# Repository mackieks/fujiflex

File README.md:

<picture> <source media="(prefers-color-scheme: dark)" srcset="images/logo.png">  </picture> 

OSHW GCVideo DVI flex for Nintendo Wii. Tested and working! Solderpad Hardware License v2.1

Special thanks to [loopj](https://github.com/loopj) for testing the FPC and writing the assembly+install documentation!

## fujiflex features
- [x] Compact 28 x 30mm 2-layer flex PCB (requires KiCAD 8.0 or later)
- [x] ~$10 BOM cost
- [x] Powered from 3.3V and 1.8V (1.2V generated from 1.8V)
- [x] 34mA @ 3.3V + 63mA @ 1.8V = 225mW power consumption
- [x] 19-pin Molex 5052781933 / 5052781970 ZIF for HDMI output
- [x] Wii SDA and SCL testpoints
- [x] MODE solder jumper
- [x] Powered by [Ingo Korb's](https://github.com/ikorb) [GCVideo DVI](https://github.com/ikorb/gcvideo/)

## Ordering & Assembly
- Download the latest gerber ZIP from [the gerbers folder](https://github.com/mackieks/fujiflex/tree/main/Gerbers).
- Order design as a 2-layer flexible PCB from JLCPCB, PCBWay, GoldPhoenix, or OSHPark.
- **MANDATORY:** FPC must use at least **0.5oz/in² copper** 
- If ordering from JLCPCB, you **must** select **0.12mm thickness** to get 0.5oz!
- A steel solderpaste stencil with etching or electropolishing is **highly** recommended for assembly. JLCPCB is a good source.

I maintain [a Mouser project](https://www.mouser.com/ProjectManager/ProjectDetail.aspx?AccessID=5589d512f3) with most of the BOM. You still need to source the FPGA from elsewhere. I suggest either [LCSC](https://www.lcsc.com/product-detail/Programmable-Logic-Device-CPLDs-FPGAs_XILINX-XC3S200A-4VQG100C_C1521645.html), [AliExpress](https://www.aliexpress.us/item/3256805017536134.html), or [Taobao](https://item.taobao.com/item.htm?abbucket=5&id=749261010737&ns=1&spm=a21n57.1.0.0.2b93523ch7BSfI).

The total BOM cost for fujiflex is around 10USD. **If you're paying more than $5 per FPGA, you are being ripped off!**

Use the provided [ibom.html](https://github.com/mackieks/fujiflex/blob/main/ibom.html) to guide part placement.

**Note:** If you intend to program the SPI flash in-system, do not place R6. You will need to place it after programming is complete.

## Flashing GCVideo

Once assembled, you'll need to flash the GCVideo bitstream. The cheap 'n' easy approach is to program *in-system* using a SPI flash programmer (EZP20xx, CH341A-based, RPi Pico) soldered to the testpads on fujiflex.

- Remove R6 to avoid powering the FPGA during programming
- Wire the CS, MISO, MOSI, CLK, and GND pads to the corresponding pins on your SPI flash programmer
- Wire the rightmost pad of R6 to 3.3V on your SPI flash programmer
- Download the *shuriken-v3-wii* bitstream from [GCVideo's latest release](https://github.com/ikorb/gcvideo/releases/latest)
- Write the bitstream (eg. `gcvideo-dvi-shuriken-v3-wii-3.1-spirom-complete.bin`) to the SPI flash (see below)
- Populate R6 (0402 0Ω)

### EZP20xx programmers

If you are using an EZP20xx programmer, you can flash the bitstream using the [Windows software](https://www.chipsetpro.com/en/content/7-download-software) for these devices.

### Other programmers (using `flashrom`)

For other programmers, [flashrom](https://flashrom.org) is an open source command line tool for programming flash chips which supports [tons of devices](https://wiki.flashrom.org/Supported_programmers), including the inexpensive CH341A-based boards.

First expand the GCVideo bitstream to match the size of the SPI flash chip:

```sh
fallocate -l 512k gcvideo-dvi-shuriken-v3-wii-3.1-spirom-complete.bin
````

Then flash the bitstream, for example with a CH341A programmer:

```sh
flashrom --programmer ch341a_spi -w gcvideo-dvi-shuriken-v3-wii-3.1-spirom-complete.bin
```

### Socket adapters

You can also use a DFN8 2x3mm socket to program the SPI flash before soldering it to the board. [Type 1](https://www.aliexpress.us/item/3256802266989931.html), [Type 2](https://www.aliexpress.us/item/3256801780444965.html)

## Installation

fujiflex is soldered directly to the [digital A/V vias](https://github.com/ikorb/gcvideo/blob/main/HDL/gcvideo_dvi/README-Wii.md#digital-audio-and-video) on a 4-layer Wii motherboard.

- Align and solder fujiflex to the GPU vias
- Wire the 1.8V, 3.3V, 5V, and GND pads
- To use a Gamecube controller for navigating the GCVideo OSD, you'll also need to [wire the GCC pad](https://github.com/ikorb/gcvideo/blob/main/HDL/gcvideo_dvi/README-Wii.md#controller) (or [via](https://bitbuilt.net/forums/index.php?threads/the-definitive-wii-trimming-guide.198/#:~:text=GameCube%20controllers%E2%80%8B,GameCube%20controllers)).

Installation Photo:

## License

Solderpad Hardware License v2.1

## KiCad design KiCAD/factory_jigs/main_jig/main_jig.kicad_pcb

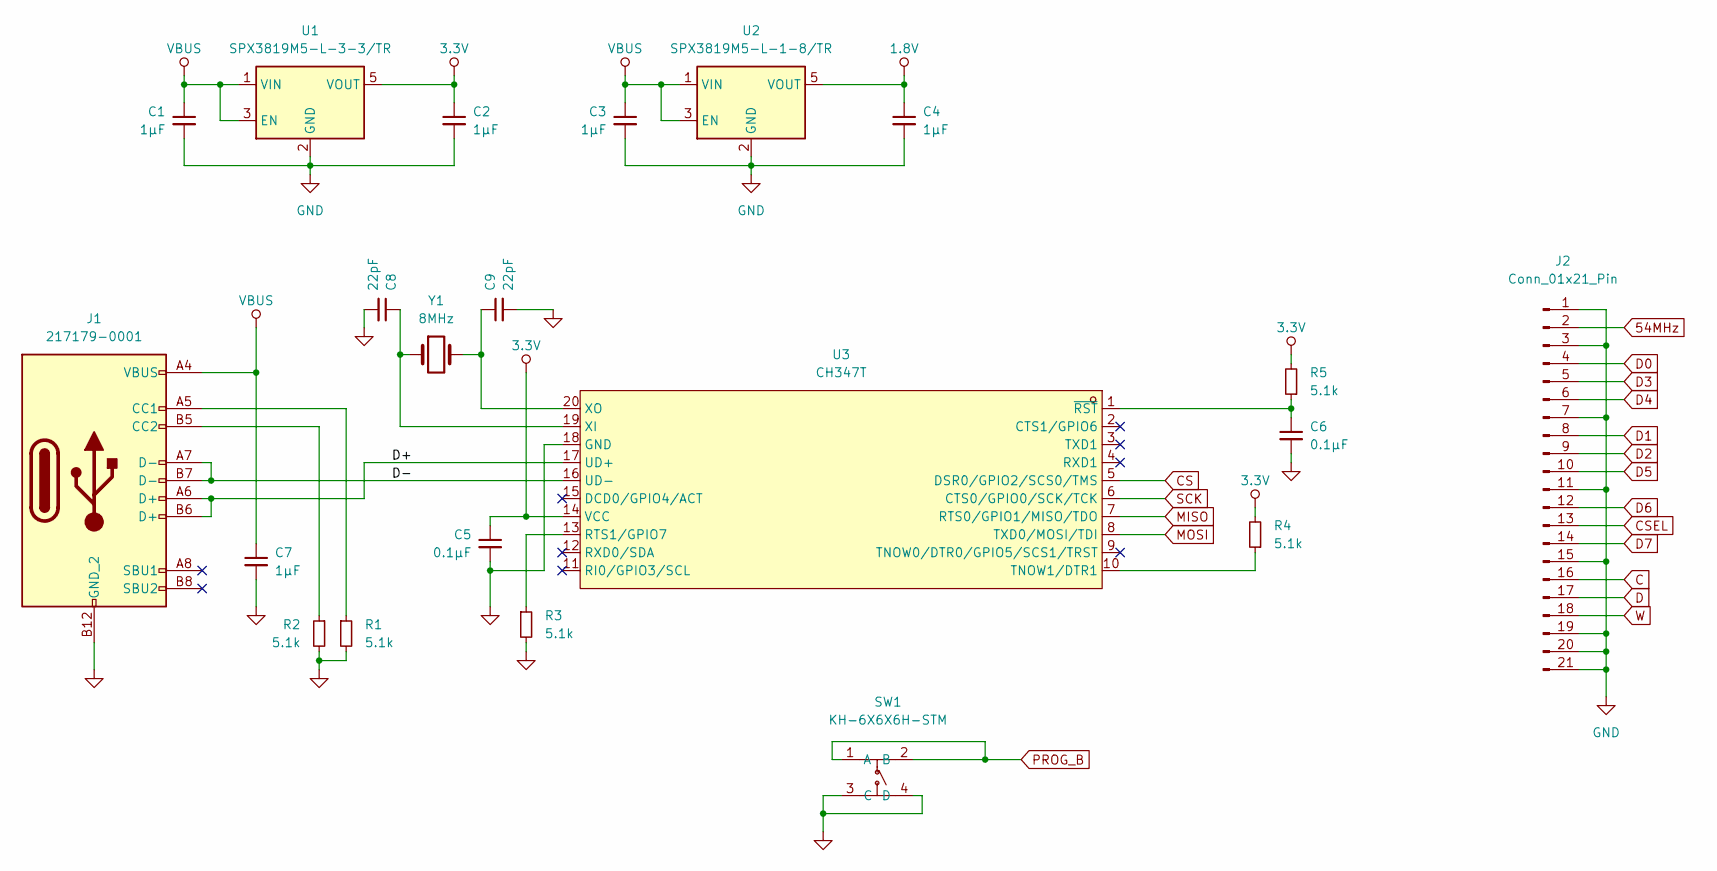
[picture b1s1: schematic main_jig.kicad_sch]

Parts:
C1, C2, C3, C4, C7: 1µF; C_0402_1005Metric
C5, C6: 0.1µF; C_0402_1005Metric
C8, C9: 22pF; C_0402_1005Metric
J1: 217179-0001; USB-C_SMD-TYPE-C-31-M-12
J2: Conn_01x21_Pin; FPC-SMD_19P-P0.50_AFD01-S19FCA-00
R1, R2, R3, R4, R5: 5.1k; R_0402_1005Metric
SW1: KH-6X6X6H-STM; SW-SMD_4P-L6.0-W6.0-P4.50-LS9.0-3; LCSC Part C2837532
U1: SPX3819M5-L-3-3/TR; SOT-23-5
U2: SPX3819M5-L-1-8/TR; SOT-23-5
U3: CH347T; TSSOP-20_L6.5-W4.4-P0.65-LS6.4-BL; LCSC Part C5122332
Y1: 8MHz; Crystal_SMD_5032-2Pin_5.0x3.2mm

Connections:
1.8V: C4.1, U2.5 (VOUT)
3.3V: C2.1, C5.1, R4.2, R5.2, U1.5 (VOUT), U3.14 (VCC)
54MHz: J2.2
/D+: J1.A6 (D+), J1.B6 (D+), U3.17 (UD+)
/D-: J1.A7 (D-), J1.B7 (D-), U3.16 (UD-)
C: J2.16
CS: U3.5 (DSR0/GPIO2/SCS0/TMS)
CSEL: J2.13
D: J2.17
D0: J2.4
D1: J2.8
D2: J2.9
D3: J2.5
D4: J2.6
D5: J2.10
D6: J2.12
D7: J2.14
GND: C1.2, C2.2, C3.2, C4.2, C5.2, C6.2, C7.2, C8.2, C9.2, J1.0 (GND_2), J1.1 (GND_2), J1.2 (GND_2), J1.3 (GND_2), J1.A1 (GND_2), J1.A12 (GND_2), J1.B1 (GND_2), J1.B12 (GND_2), J2.1, J2.3, J2.7, J2.11, J2.15, J2.19, J2.20, J2.21, R1.2, R2.2, R3.2, SW1.3 (C), SW1.4 (D), U1.2 (GND), U2.2 (GND), U3.18 (GND)
MISO: U3.7 (RTS0/GPIO1/MISO/TDO)
MOSI: U3.8 (TXD0/MOSI/TDI)
unnamed: J1.A5 (CC1), R1.1
unnamed: J1.B5 (CC2), R2.1
unnamed: R3.1, U3.13 (RTS1/GPIO7)
unnamed: R4.1, U3.10 (TNOW1/DTR1)
unnamed: C8.1, U3.19 (XI), Y1.1
unnamed: C9.1, U3.20 (XO), Y1.2
unnamed: C6.1, R5.1, U3.1 (~RST)
PROG_B: SW1.1 (A), SW1.2 (B)
SCK: U3.6 (CTS0/GPIO0/SCK/TCK)
VBUS: C1.1, C3.1, C7.1, J1.A4 (VBUS), J1.A9 (VBUS), J1.B4 (VBUS), J1.B9 (VBUS), U1.1 (VIN), U1.3 (EN), U2.1 (VIN), U2.3 (EN)
W: J2.18

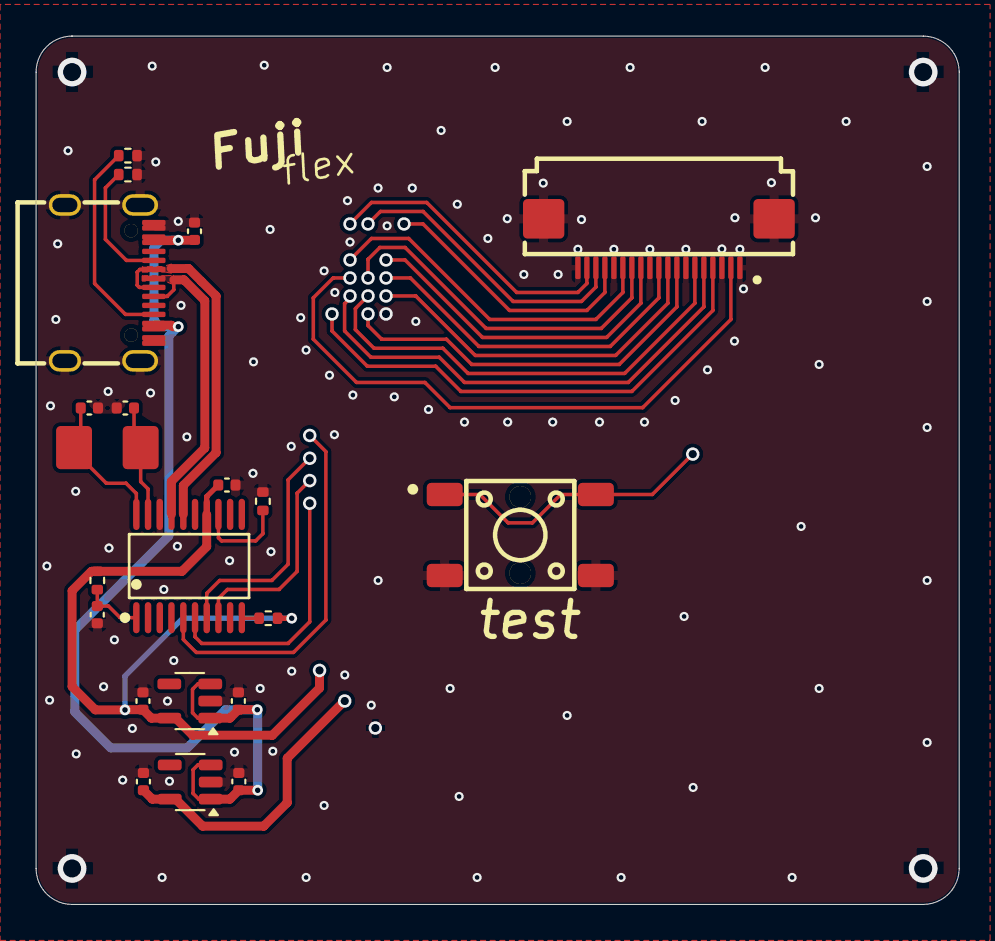
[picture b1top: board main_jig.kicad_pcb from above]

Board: 2 copper layers, 51.3 x 48.2 mm, 21 parts (0 on the bottom side), 14 nets.

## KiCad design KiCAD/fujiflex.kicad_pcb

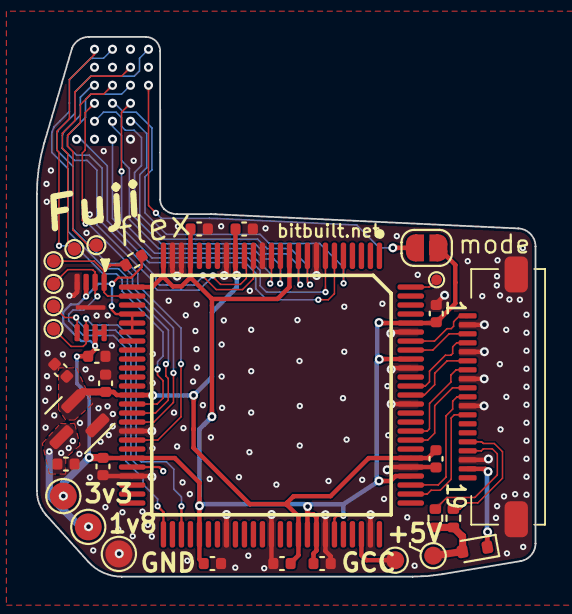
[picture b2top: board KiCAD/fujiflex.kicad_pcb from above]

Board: 2 copper layers, 27.7 x 30.0 mm, 33 parts (0 on the bottom side), 22 nets.

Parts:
C1, C2: 1uF; C_0402_1005Metric
C3, C4, C5, C6, C7, C8, C9, C10, C11, C12: 0.1uF; C_0402_1005Metric
D1: BAT54XV2T1G; D_SOD-523
J1: 505278-1933; 5052781933
JP1: SolderJumper_2_Open; SolderJumper-2_P1.3mm_Open_RoundedPad1.0x1.5mm
R1, R2, R3: 10k; R_0402_1005Metric
TP1, TP6, TP7, TP9, TP10, TP11, TP12: TestPoint; TestPoint_Pad_D0.75mm
TP2, TP3, TP4: TestPoint; TestPoint_Pad_D1.5mm
TP5, TP8: TestPoint; TestPoint_Pad_D1.0mm
U1: TPS7A0512PDBZR; SOT-23
U2: XC3S200A-4VQG100C; QFP50P1600X1600X120-100N
U3: AT25SF041B-MAHD-T; SON50P300X200X60-9N-D

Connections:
+1V2: C2.1, C3.1, C4.1, C5.1, C6.1, U1.2 (VO), U2.17 (VCCINT_1), U2.38 (VCCINT_2), U2.66 (VCCINT_3), U2.81 (VCCINT_4)
+1V8: C1.1, TP4.1, U1.3 (VI)
+3.3V: C7.1, C8.1, C9.1, C10.1, C11.1, C12.1, JP1.2 (B), R3.1, TP3.1, U2.11 (VCCO_3), U2.22 (VCCAUX_1), U2.25 (IO_L01N_2/M0), U2.26 (VCCO_2_1), U2.29 (IO_L03N_2/VS2), U2.30 (IO_L04P_2/VS1), U2.31 (IO_L04N_2/VS0), U2.45 (VCCO_2_2), U2.55 (VCCAUX_2), U2.67 (VCCO_1), U2.68 (IP_1/VREF_1), U2.70 (IO_L05P_1), U2.79 (VCCO_0_1), U2.92 (VCCAUX_3), U2.96 (VCCO_0_2), U3.3 (~WP_(IO2)), U3.7 (~HOLD_(IO3)), U3.8 (VCC)
+5V: D1.2 (A), R1.1, R2.1, TP5.1
CLK: TP12.1, U2.53 (IO_L12N_2/CCLK), U3.6 (SCK)
CS: R3.2, TP9.1, U2.27 (IO_L02N_2/CSO_B), U3.1 (~CS)
GCC: TP8.1, U2.73 (IO_L06N_1)
GND: C1.2, C2.2, C3.2, C4.2, C5.2, C6.2, C7.2, C8.2, C9.2, C10.2, C11.2, C12.2, J1.3, J1.9, J1.12, J1.15, J1.18, J1.MP1, J1.MP2, TP2.1, U1.1 (GND), U2.8 (GND_1), U2.14 (GND_2), U2.18 (GND_3), U2.23 (IO_L01P_2/M1), U2.24 (IO_L02P_2/M2), U2.42 (GND_4), U2.47 (GND_5), U2.58 (GND_6), U2.63 (GND_7), U2.69 (GND_8), U2.74 (GND_9), U2.80 (GND_10), U2.87 (GND_11), U2.91 (GND_12), U2.95 (GND_13), U3.4 (GND), U3.9 (EP)
MISO: TP11.1, U2.51 (IO_L12P_2/D0/DIN/MISO), U3.2 (SO_(IO1))
MOSI: TP10.1, U2.46 (IO_2/MOSI/CSI_B), U3.5 (SI_(IO0))
unnamed: D1.1 (K), J1.2
unnamed: J1.4, R2.2
unnamed: J1.5, R1.2
unnamed: TP1.1, U2.100 (PROG_B)
TMDS0+: J1.13, U2.84 (IO_L02N_0/GCLK5)
TMDS0-: J1.11, U2.83 (IO_L02P_0/GCLK4)
TMDS1+: J1.16, U2.89 (IO_L04N_0/GCLK9)
TMDS1-: J1.14, U2.88 (IO_L04P_0/GCLK8)
TMDS2+: J1.19, U2.94 (IO_L05N_0)
TMDS2-: J1.17, U2.93 (IO_L05P_0)
TMDSClk+: J1.10, U2.78 (IO_L01N_0)
TMDSClk-: J1.8, U2.77 (IO_L01P_0/VREF_0)

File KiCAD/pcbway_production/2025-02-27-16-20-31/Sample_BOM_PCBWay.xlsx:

|  |  | fujiflex_2025-02-27 100PCS BOM
Item # | Designator | Qty | Manufacturer | Mfg Part # | Description / Value | Package/Footprint | Type | Your Instructions / Notes
1 | C1, C2 | 2 |  |  | 1uF 25V X5R | C0402 | smt
2 | C10, C11, C12, C3, C4, C5, C6, C7, C8, C9 | 10 |  |  | 0.1uF 16V X7R | C0402 | smt
3 | D1 | 1 | SLKORMICRO Elec | 1N5819WT | Schottky Diode | SOD-523 | smt
4 | J1 | 1 | Molex | 505278-1933 |  |  | smt | [Supplied by customer客供]
5 | R1, R2, R3 | 3 |  |  | 10kΩ 1% | R0402 | smt
6 | U1 | 1 | Lewa Micro | LW5912N23D | 1.2V output LDO regulator | SOT-23-3L | smt
7 | U2 | 1 | Xilinx / AMD | XC3S200A-4VQG100C | Spartan-3A FPGA | TQFP-100 | smt | [Supplied by customer客供]
8 | U3 | 1 | PUYA | P25Q40H-UXH-IR | 4Mbit SPI flash | USON-8-EP(2x3) | smt | [Supplied by customer客供]
9
10
11
12
13
14
15

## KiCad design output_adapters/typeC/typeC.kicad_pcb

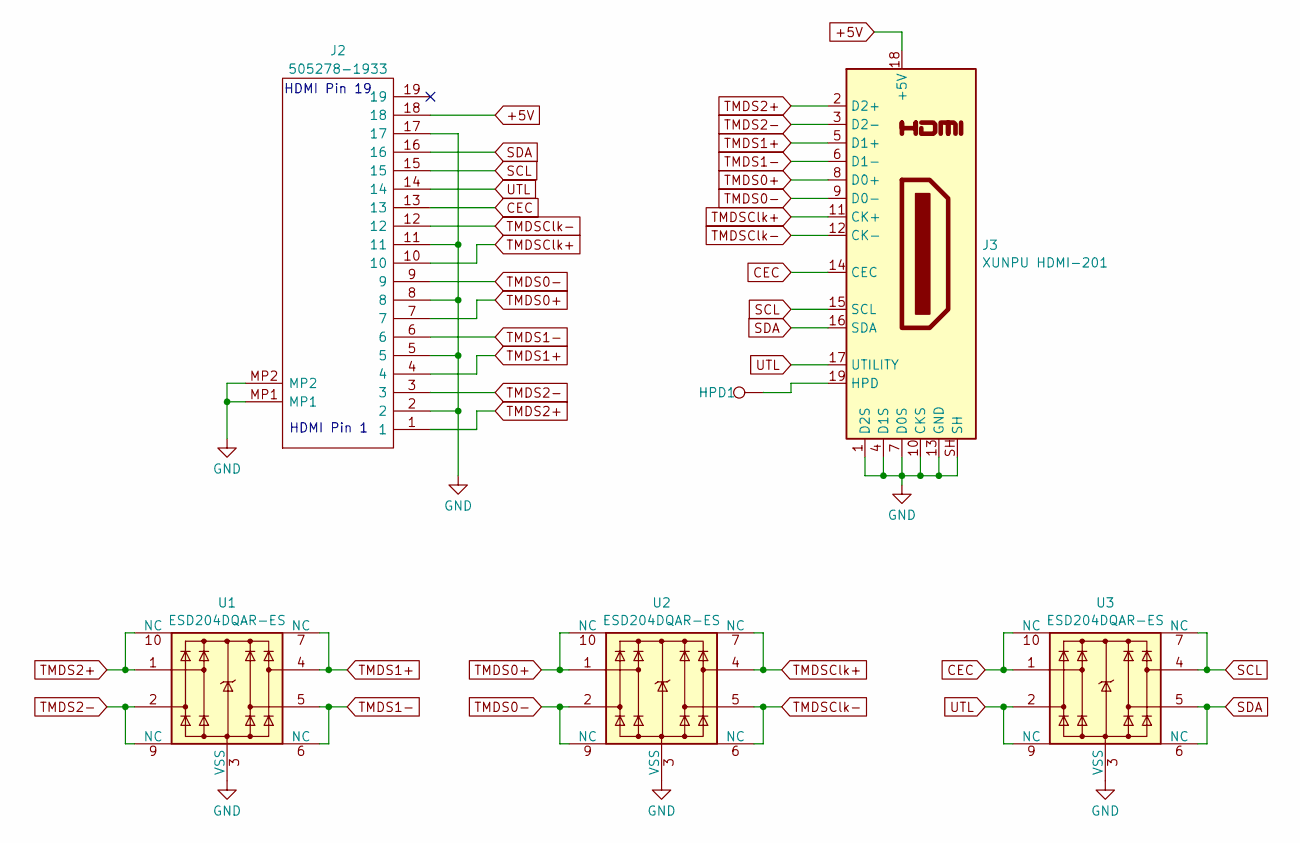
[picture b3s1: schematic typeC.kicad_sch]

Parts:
HPD1: TestPoint; TestPoint_Pad_D1.0mm
J2: 505278-1933; 5052781933; Mouser Part Number 538-505278-1933
J3: XUNPU HDMI-201; 685119136923
U1, U2, U3: ESD204DQAR-ES; Diodes_UDFN-10_1.0x2.5mm_P0.5mm

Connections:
+5V: J2.18, J3.18 (+5V)
CEC: J2.13, J3.14 (CEC), U3.1, U3.10 (NC)
GND: J2.2, J2.5, J2.8, J2.11, J2.17, J2.MP1, J2.MP2, J3.1 (D2S), J3.4 (D1S), J3.7 (D0S), J3.10 (CKS), J3.13 (GND), J3.SH, U1.3 (VSS), U1.8 (VSS), U2.3 (VSS), U2.8 (VSS), U3.3 (VSS), U3.8 (VSS)
unnamed: HPD1.1, J3.19 (HPD)
SCL: J2.15, J3.15 (SCL), U3.4, U3.7 (NC)
SDA: J2.16, J3.16 (SDA), U3.5, U3.6 (NC)
TMDS0+: J2.7, J3.8 (D0+), U2.1, U2.10 (NC)
TMDS0-: J2.9, J3.9 (D0-), U2.2, U2.9 (NC)
TMDS1+: J2.4, J3.5 (D1+), U1.4, U1.7 (NC)
TMDS1-: J2.6, J3.6 (D1-), U1.5, U1.6 (NC)
TMDS2+: J2.1, J3.2 (D2+), U1.1, U1.10 (NC)
TMDS2-: J2.3, J3.3 (D2-), U1.2, U1.9 (NC)
TMDSClk+: J2.10, J3.11 (CK+), U2.4, U2.7 (NC)
TMDSClk-: J2.12, J3.12 (CK-), U2.5, U2.6 (NC)
UTL: J2.14, J3.17 (UTILITY), U3.2, U3.9 (NC)

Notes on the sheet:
HDMI Pin 19
HDMI Pin 1

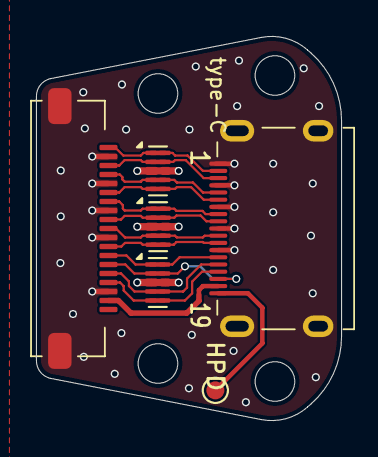
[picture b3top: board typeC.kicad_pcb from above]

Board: 2 copper layers, 16.9 x 21.3 mm, 6 parts (0 on the bottom side), 15 nets.

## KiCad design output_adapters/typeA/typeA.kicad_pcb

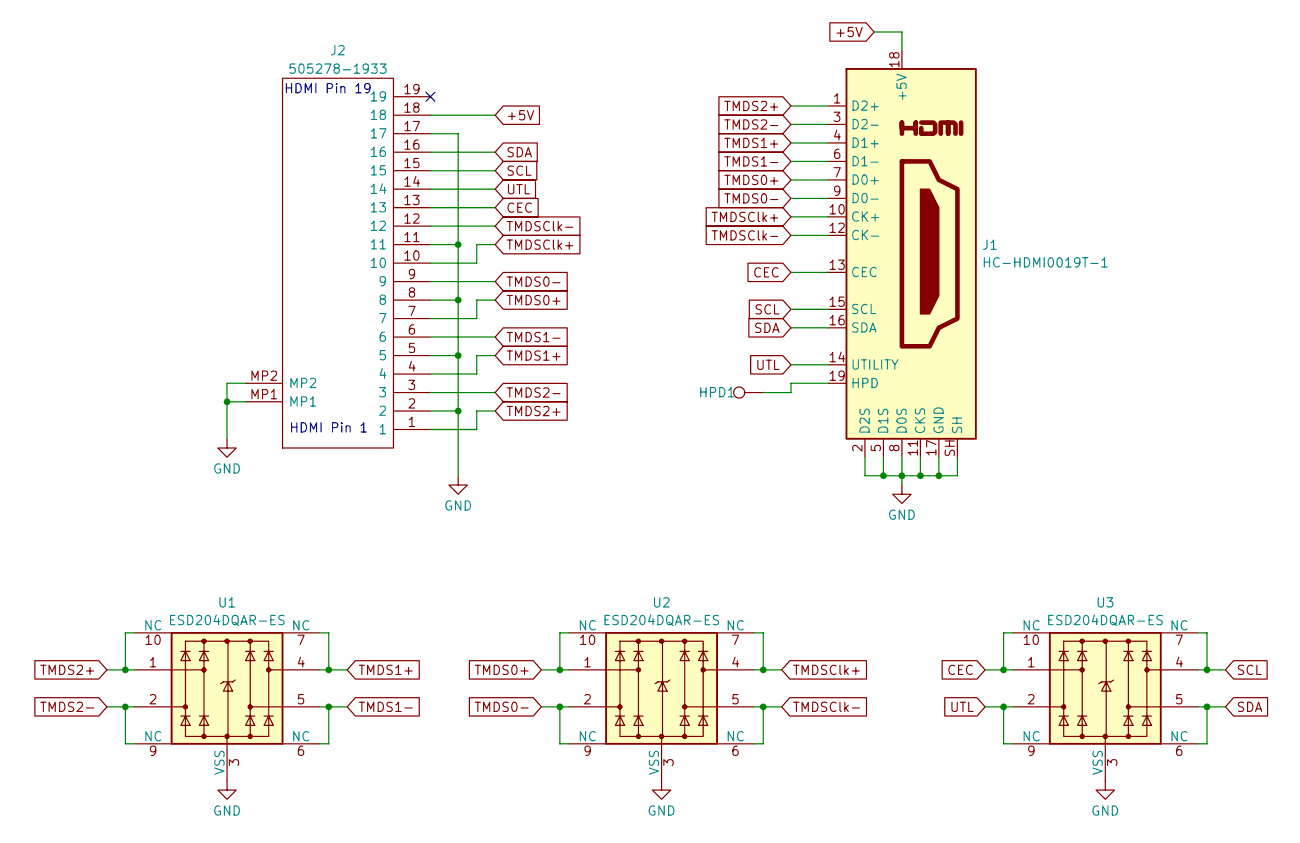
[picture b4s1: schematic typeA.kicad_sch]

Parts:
HPD1: TestPoint; TestPoint_Pad_D1.0mm
J1: HC-HDMI0019T-1; HDMI_A_Molex_208658-1001_Horizontal
J2: 505278-1933; 5052781933; Mouser Part Number 538-505278-1933
U1, U2, U3: ESD204DQAR-ES; Diodes_UDFN-10_1.0x2.5mm_P0.5mm

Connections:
+5V: J1.18 (+5V), J2.18
CEC: J1.13 (CEC), J2.13, U3.1, U3.10 (NC)
GND: J1.2 (D2S), J1.5 (D1S), J1.8 (D0S), J1.11 (CKS), J1.17 (GND), J1.SH, J2.2, J2.5, J2.8, J2.11, J2.17, J2.MP1, J2.MP2, U1.3 (VSS), U1.8 (VSS), U2.3 (VSS), U2.8 (VSS), U3.3 (VSS), U3.8 (VSS)
unnamed: HPD1.1, J1.19 (HPD)
SCL: J1.15 (SCL), J2.15, U3.4, U3.7 (NC)
SDA: J1.16 (SDA), J2.16, U3.5, U3.6 (NC)
TMDS0+: J1.7 (D0+), J2.7, U2.1, U2.10 (NC)
TMDS0-: J1.9 (D0-), J2.9, U2.2, U2.9 (NC)
TMDS1+: J1.4 (D1+), J2.4, U1.4, U1.7 (NC)
TMDS1-: J1.6 (D1-), J2.6, U1.5, U1.6 (NC)
TMDS2+: J1.1 (D2+), J2.1, U1.1, U1.10 (NC)
TMDS2-: J1.3 (D2-), J2.3, U1.2, U1.9 (NC)
TMDSClk+: J1.10 (CK+), J2.10, U2.4, U2.7 (NC)
TMDSClk-: J1.12 (CK-), J2.12, U2.5, U2.6 (NC)
UTL: J1.14 (UTILITY), J2.14, U3.2, U3.9 (NC)

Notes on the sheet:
HDMI Pin 19
HDMI Pin 1

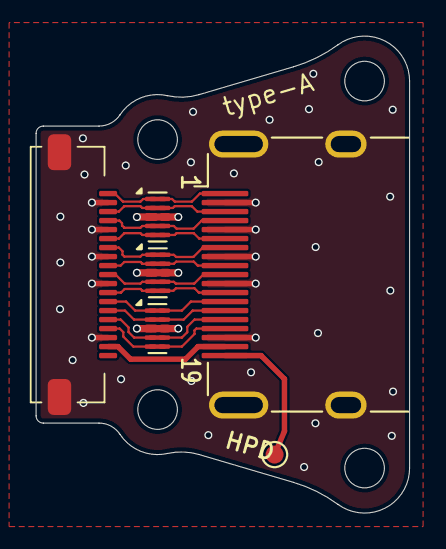
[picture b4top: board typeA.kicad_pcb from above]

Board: 2 copper layers, 20.8 x 26.5 mm, 6 parts (0 on the bottom side), 15 nets.

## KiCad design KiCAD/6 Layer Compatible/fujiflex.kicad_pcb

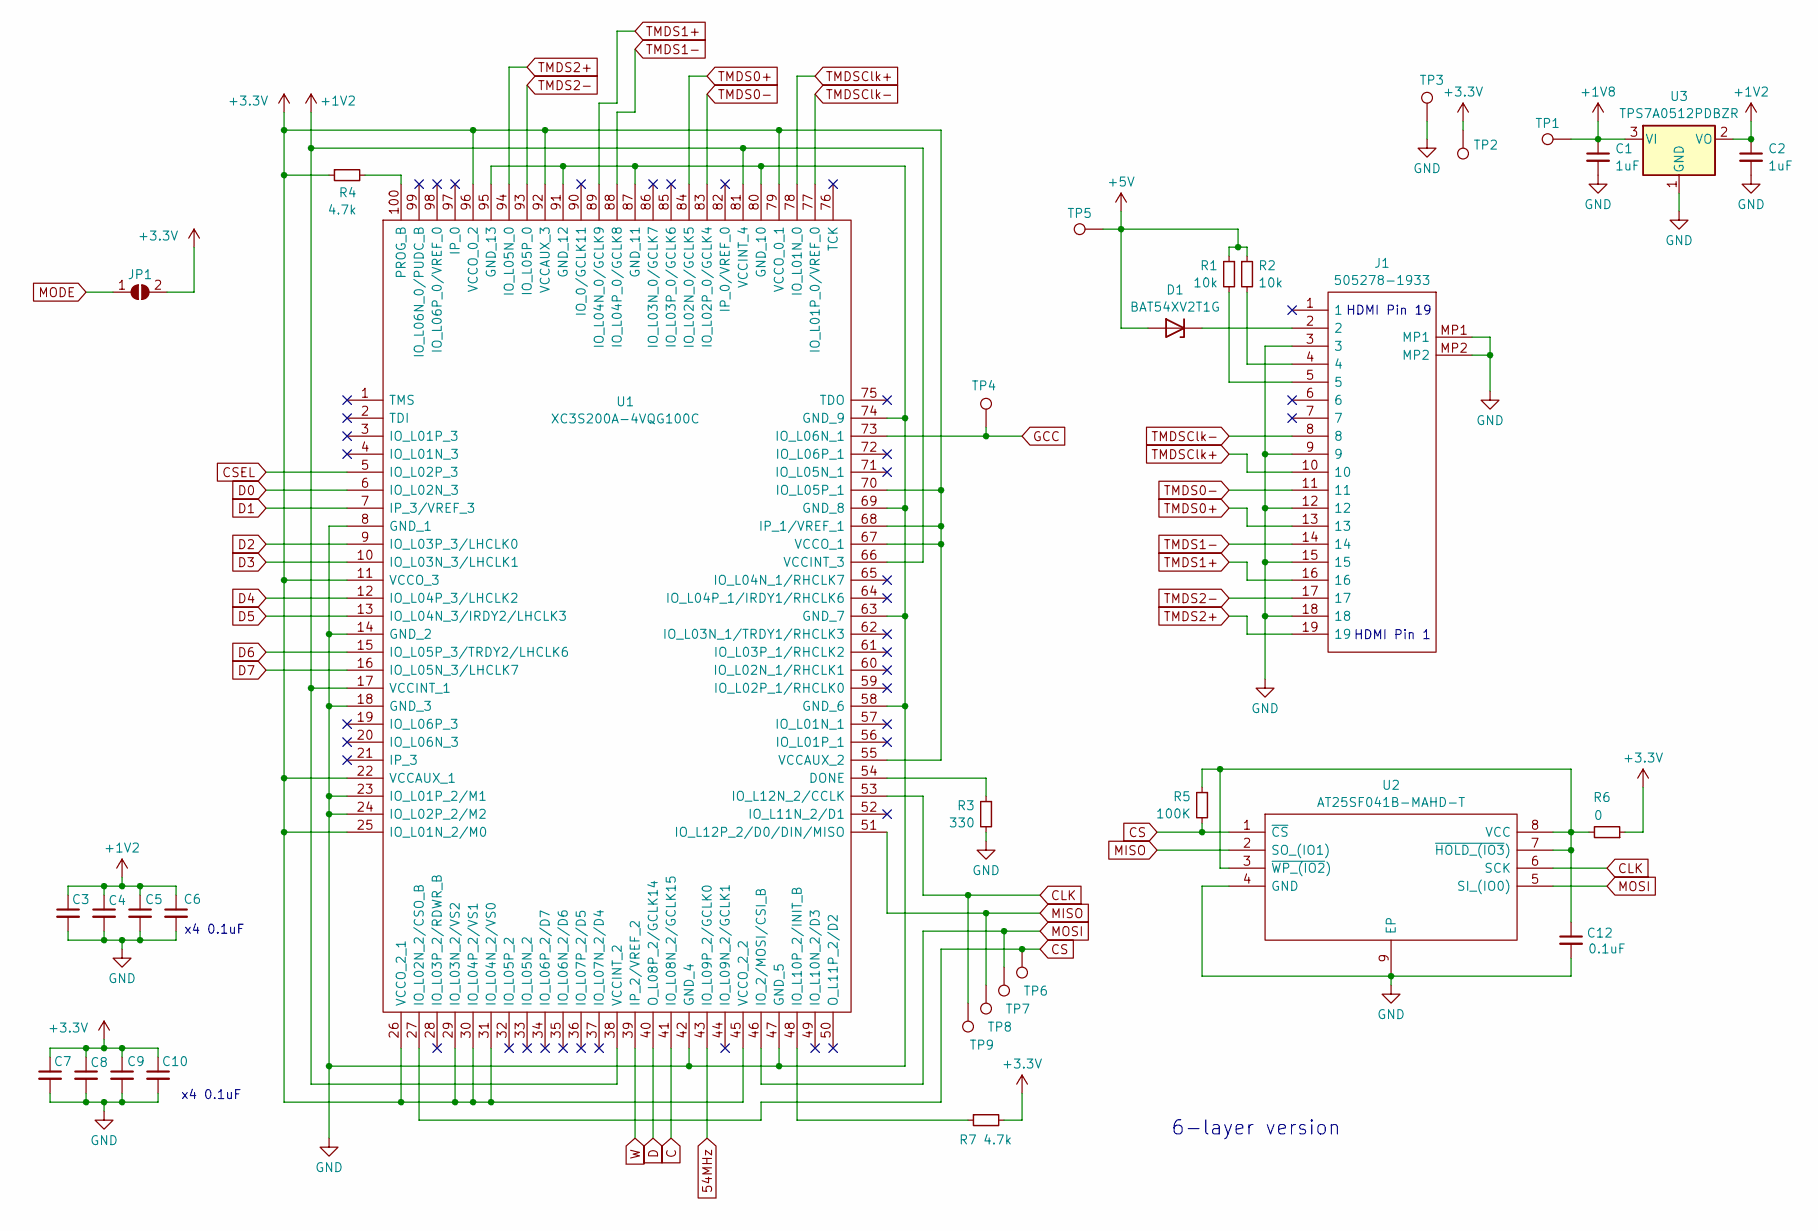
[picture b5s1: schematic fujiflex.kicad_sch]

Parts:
C1, C2: 1uF; C_0402_1005Metric
C3, C4, C5, C6, C7, C8, C9, C10, C12: 0.1uF; C_0402_1005Metric
D1: BAT54XV2T1G; D_SOD-523
J1: 505278-1933; 5052781933; Mouser Part Number 538-505278-1933
JP1: SolderJumper_2_Open; SolderJumper-2_P1.3mm_Open_RoundedPad1.0x1.5mm
R1, R2: 10k; R_0402_1005Metric
R3: 330; R_0402_1005Metric
R4, R7: 4.7k; R_0402_1005Metric
R5: 100K; R_0402_1005Metric
R6: 0; R_0402_1005Metric
TP1, TP2, TP3: TestPoint; TestPoint_Pad_D1.5mm
TP4, TP5: TestPoint; TestPoint_Pad_D1.0mm
TP6, TP7, TP8, TP9: TestPoint; TestPoint_Pad_D0.75mm
U1: XC3S200A-4VQG100C; QFP50P1600X1600X120-100N; Mouser Part Number 217-C3S200A-4VQG100C
U2: AT25SF041B-MAHD-T; SON50P300X200X60-9N-D; Mouser Part Number 988-AT25SF041BMAHDT
U3: TPS7A0512PDBZR; SOT-23

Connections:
54MHz: U1.43 (IO_L09P_2/GCLK0)
+1V2: C2.1, C3.1, C4.1, C5.1, C6.1, U1.17 (VCCINT_1), U1.38 (VCCINT_2), U1.66 (VCCINT_3), U1.81 (VCCINT_4), U3.2 (VO)
+1V8: C1.1, TP1.1, U3.3 (VI)
+3.3V: C7.1, C8.1, C9.1, C10.1, JP1.2 (B), R4.1, R6.1, R7.2, TP2.1, U1.11 (VCCO_3), U1.22 (VCCAUX_1), U1.25 (IO_L01N_2/M0), U1.26 (VCCO_2_1), U1.29 (IO_L03N_2/VS2), U1.30 (IO_L04P_2/VS1), U1.31 (IO_L04N_2/VS0), U1.45 (VCCO_2_2), U1.55 (VCCAUX_2), U1.67 (VCCO_1), U1.68 (IP_1/VREF_1), U1.70 (IO_L05P_1), U1.79 (VCCO_0_1), U1.92 (VCCAUX_3), U1.96 (VCCO_0_2)
+5V: D1.2 (A), R1.1, R2.1, TP5.1
C: U1.41 (IO_L08N_2/GCLK15)
CLK: TP9.1, U1.53 (IO_L12N_2/CCLK), U2.6 (SCK)
CS: R5.2, TP6.1, U1.27 (IO_L02N_2/CSO_B), U2.1 (~CS)
CSEL: U1.5 (IO_L02P_3)
D: U1.40 (O_L08P_2/GCLK14)
D0: U1.6 (IO_L02N_3)
D1: U1.7 (IP_3/VREF_3)
D2: U1.9 (IO_L03P_3/LHCLK0)
D3: U1.10 (IO_L03N_3/LHCLK1)
D4: U1.12 (IO_L04P_3/LHCLK2)
D5: U1.13 (IO_L04N_3/IRDY2/LHCLK3)
D6: U1.15 (IO_L05P_3/TRDY2/LHCLK6)
D7: U1.16 (IO_L05N_3/LHCLK7)
GCC: TP4.1, U1.73 (IO_L06N_1)
GND: C1.2, C2.2, C3.2, C4.2, C5.2, C6.2, C7.2, C8.2, C9.2, C10.2, C12.2, J1.3, J1.9, J1.12, J1.15, J1.18, J1.MP1, J1.MP2, R3.2, TP3.1, U1.8 (GND_1), U1.14 (GND_2), U1.18 (GND_3), U1.23 (IO_L01P_2/M1), U1.24 (IO_L02P_2/M2), U1.42 (GND_4), U1.47 (GND_5), U1.58 (GND_6), U1.63 (GND_7), U1.69 (GND_8), U1.74 (GND_9), U1.80 (GND_10), U1.87 (GND_11), U1.91 (GND_12), U1.95 (GND_13), U2.4 (GND), U2.9 (EP), U3.1 (GND)
MISO: TP8.1, U1.51 (IO_L12P_2/D0/DIN/MISO), U2.2 (SO_(IO1))
MODE: JP1.1 (A)
MOSI: TP7.1, U1.46 (IO_2/MOSI/CSI_B), U2.5 (SI_(IO0))
unnamed: D1.1 (K), J1.2
unnamed: J1.4, R2.2
unnamed: J1.5, R1.2
unnamed: R3.1, U1.54 (DONE)
unnamed: R7.1, U1.48 (IO_L10P_2/INIT_B)
unnamed: R4.2, U1.100 (PROG_B)
unnamed: C12.1, R5.1, R6.2, U2.3 (~WP_(IO2)), U2.7 (~HOLD_(IO3)), U2.8 (VCC)
TMDS0+: J1.13, U1.84 (IO_L02N_0/GCLK5)
TMDS0-: J1.11, U1.83 (IO_L02P_0/GCLK4)
TMDS1+: J1.16, U1.89 (IO_L04N_0/GCLK9)
TMDS1-: J1.14, U1.88 (IO_L04P_0/GCLK8)
TMDS2+: J1.19, U1.94 (IO_L05N_0)
TMDS2-: J1.17, U1.93 (IO_L05P_0)
TMDSClk+: J1.10, U1.78 (IO_L01N_0)
TMDSClk-: J1.8, U1.77 (IO_L01P_0/VREF_0)
W: U1.39 (IP_2/VREF_2)

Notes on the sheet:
6-layer version
HDMI Pin 1
x4 0.1uF
HDMI Pin 19

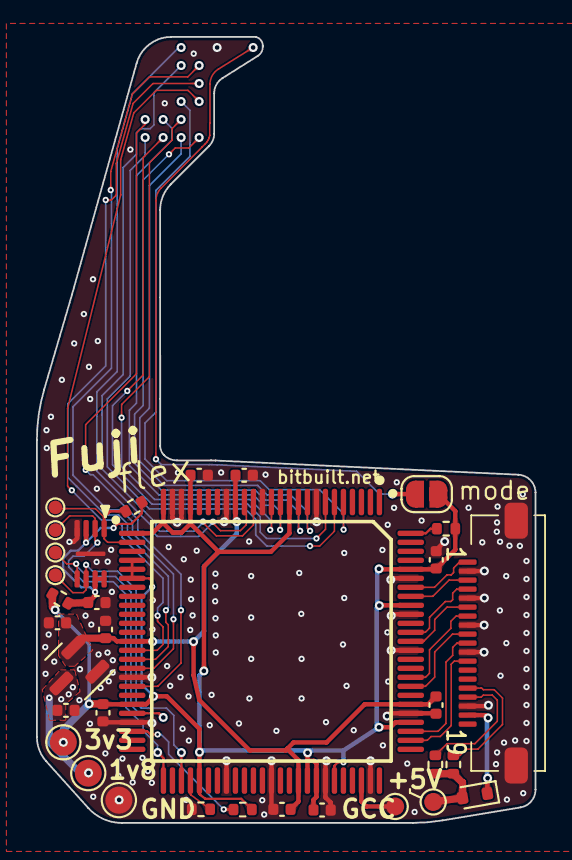
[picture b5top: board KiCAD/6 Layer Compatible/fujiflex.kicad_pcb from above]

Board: 2 copper layers, 27.7 x 43.7 mm, 33 parts (0 on the bottom side), 25 nets.

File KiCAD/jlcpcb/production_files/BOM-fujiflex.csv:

Comment,Designator,Footprint,LCSC
0.1uF,"C10,C12,C3,C4,C5,C6,C7,C8,C9",C_0402_1005Metric,C1525
AT25SF041B-MAHD-T,U2,SON50P300X200X60-9N-D,C16197313
0,R6,R_0402_1005Metric,C17168
330,R3,R_0402_1005Metric,C25104
100K,R5,R_0402_1005Metric,C25741
4.7k,"R1,R2,R4,R7",R_0402_1005Metric,C25940
505278-1933,J1,5052781933,C2925372
TPS7A0512PDBZR,U3,SOT-23,C2992063
1uF,"C1,C2",C_0402_1005Metric,C52923
BAT54XV2T1G,D1,D_SOD-523,C5451630
XC3S200A-4VQG100C,U1,QFP50P1600X1600X120-100N,

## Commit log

2024-02-11 rearrange
2024-02-11 fix via
2024-02-11 moar stitching vias
2024-02-11 fix schematic
2024-02-12 add 6layer version
2024-02-13 minor routing fixes
2024-02-14 fix LDO blunder
2024-03-12 pcb fixes
    - tie IR button pin high
    - minor layout/routing tweaks
    - silkscreen edits
    - updated gerbers
2024-03-14 Add some basic assembly, flashing, and installation docs
2024-03-14 Remove bullet points to avoid scrolling
2024-03-16 minor layout updates
    -updated grounding and some via sizes
    -fixed IR button on 6L version
    -updated gerbers
2024-03-16 update plot, gitignore
2024-04-11 add type-A adapter
2024-04-11 add typeA img
2024-04-11 add dimensions
2024-04-11 add typeC adapter
2024-04-11 working on JLC PCBA files
2025-02-02 update to 9
2025-02-02 embed fonts + 3d, update gerbers
2025-02-02 embed 3d
2025-02-27 pcbway prod files
2025-03-06 progress on factory test jig
